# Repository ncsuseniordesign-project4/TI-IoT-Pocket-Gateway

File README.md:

# TI-IoT-Pocket-Gateway

Please see the [wiki](https://github.com/ncsuseniordesign-project4/TI-IoT-Pocket-Gateway/wiki) as well!

## Hardware

Hardware design files can be found under the `hardware` folder. You will need AutoCAD Eagle to modify these files.

CAM Data:
   The up to day CAM outputs are in the zipped file "IoT_Pocket_Gateway_Final.zip". 

## Software

Demo scripts, testing tools, etc can be found under the `software` folder, including a simple demo web app for communicating with a remote device using the Azure IoT Hub.

## Configuration

A `systemd` service for modem configuration / management can be found under the `configuration` folder. The various demo scripts in the `software` folder also provide examples showing how the buttons and LEDs can be used. Please see the [wiki](https://github.com/ncsuseniordesign-project4/TI-IoT-Pocket-Gateway/wiki) as well!

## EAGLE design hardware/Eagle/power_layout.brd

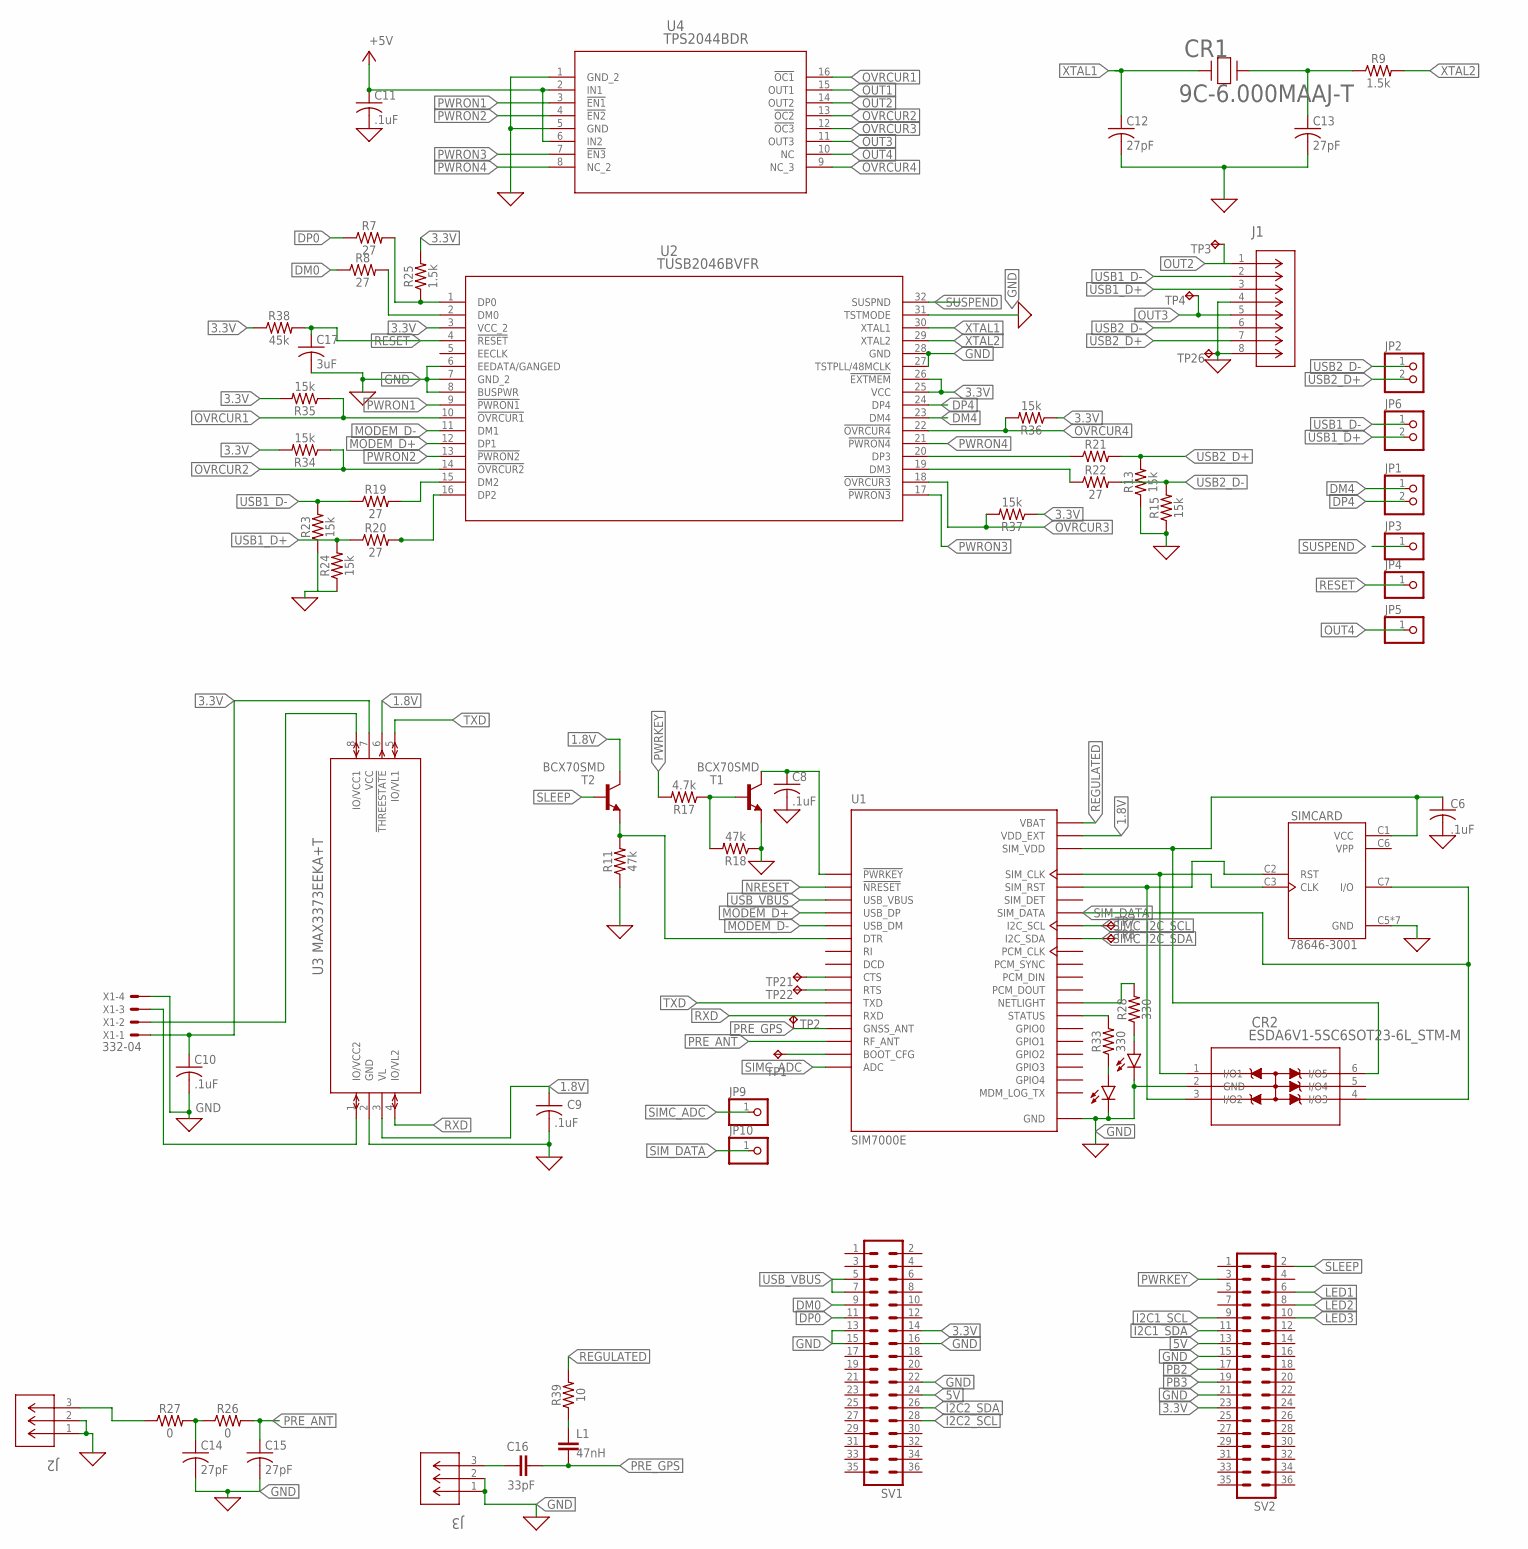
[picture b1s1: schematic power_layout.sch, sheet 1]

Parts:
C6, C8, C9, C10, C11: .1uF; C0805
C12, C13, C14, C15: 27pF; C0603
C16: 33pF; C0603K
C17: 3uF; C0805
CR1: 9C-6.000MAAJ-T; CRYSTAL_TXC_9C_TXC
CR2: ESDA6V1-5SC6SOT23-6L_STM-M; SOT23-6L_STM-M
D4, D5: Yellow; LED-0603
J1: AU-Y1008-2; CONN_AU-Y1008-2_ASM
J2, J3: U.FL-R-SMT-1(01); CONN_-SMT-1(01)
JP1, JP2, JP6: PINHD-1X2; 1X02
JP3, JP4, JP5, JP9, JP10: PINHD-1X1; 1X01
L1: 47nH; C1608
R7, R8, R19, R20, R21, R22: 27; 0805
R9: 1.5k; 0603
R11, R18: 47k; 0603
R13, R15, R23, R24, R34, R35, R36, R37: 15k; 0805
R17: 4.7k; 0603
R25: 1.5k; 0805
R26, R27: 0; 0603
R28, R33: 330; 0603
R38: 45k; 0805
R39: 10; 0805
SIMCARD: 78646-3001; MOLEX_78646-3001
SV1, SV2: MA18-2
T1, T2: BCX70SMD; SOT23
TP1, TP3, TP4, TP7, TP8, TP21, TP22, TP26: TPTP10R; TP10R
TP2: TPTP16R; TP16R
U1: SIM7000E; SIMCON_SIM7000E
U2: TUSB2046BVFR; VF32_TEX
U3: MAX3373EEKA+T; 21-0078H
U4: TPS2044BDR; D16_TEX
X1: 332-04

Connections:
0: R11.1; also elsewhere on the board
1.8V: C9.1, T2.3 (C), U1.15 (VDD_EXT), U3.3 (VL), U3.6 (!THREESTATE)
3.3V: C10.1, R25.2, R34.2, R35.2, R36.1, R37.1, R38.1, SV1.14, SV2.23, U2.3 (VCC_2), U2.25 (VCC), U2.26 (!EXTMEM), U3.7 (VCC), X1.1; also elsewhere on the board
5V: C11.1, SV1.24, SV2.13, U4.2 (IN1), U4.6 (IN2); also elsewhere on the board
DM0: R8.1, SV1.9
DM4: JP1.1, U2.23 (DM4)
DP0: R7.1, SV1.11
DP4: JP1.2, U2.24 (DP4)
GND: C6.2, C8.2, C9.2, C10.2, C11.2, C12.2, C13.2, C14.2, C15.2, C17.2, CR2.2 (GND), D4.C, D5.C, J1.4, J1.8, J2.1, J2.2, J3.1, J3.2, R13.1, R15.1, R18.1, R23.1, R24.1, SIMCARD.C5 (GND), SIMCARD.G1 (GND), SIMCARD.G2 (GND), SIMCARD.G3 (GND), SIMCARD.G4 (GND), SIMCARD.G5 (GND), SIMCARD.G6 (GND), SV1.13, SV1.15, SV1.16, SV1.22, SV2.15, SV2.21, T1.2 (E), TP26.TP, U1.2 (GND), U1.17 (GND), U1.18 (GND), U1.29 (GND), U1.39 (GND), U1.45 (GND), U1.46 (GND), U1.54 (GND), U1.58 (GND), U1.59 (GND), U1.61 (GND), U1.62 (GND), U1.63 (GND), U1.64 (GND), U1.65 (GND), U2.6 (EEDATA/GANGED), U2.7 (GND_2), U2.8 (BUSPWR), U2.27 (TSTPLL/48MCLK), U2.28 (GND), U2.31 (TSTMODE), U3.2 (GND), U4.1 (GND_2), U4.5 (GND), X1.4; also elsewhere on the board
I2C1_SCL: SV2.9; also elsewhere on the board
I2C1_SDA: SV2.11; also elsewhere on the board
I2C2_SCL: SV1.28; also elsewhere on the board
I2C2_SDA: SV1.26; also elsewhere on the board
LED1: SV2.6; also elsewhere on the board
LED2: SV2.8; also elsewhere on the board
LED3: SV2.10; also elsewhere on the board
MODEM_D+: U1.27 (USB_DP), U2.12 (DP1)
MODEM_D-: U1.28 (USB_DM), U2.11 (DM1)
unnamed: C6.1, CR2.6 (I/O5), SIMCARD.C1 (VCC), U1.30 (SIM_VDD)
unnamed: CR2.3 (I/O2), SIMCARD.C2 (RST), U1.33 (SIM_RST)
unnamed: CR2.1 (I/O1), SIMCARD.C3 (CLK), U1.32 (SIM_CLK)
unnamed: TP1.TP, U1.6 (BOOT_CFG)
unnamed: R7.2, R25.1, U2.1 (DP0)
unnamed: C14.1, R26.1, R27.2
unnamed: R8.2, U2.2 (DM0)
unnamed: U3.8 (IO/VCC1), X1.2
unnamed: C13.1, CR1.2, R9.1
unnamed: C16.1, J3.3
unnamed: R22.1, U2.19 (DM3)
unnamed: R17.1, R18.2, T1.1 (B)
unnamed: R19.2, U2.15 (DM2)
unnamed: R20.2, U2.16 (DP2)
unnamed: TP21.TP, U1.7 (CTS)
unnamed: R21.1, U2.20 (DP3)
unnamed: C8.1, T1.3 (C), U1.1 (!PWRKEY)
unnamed: L1.1, R39.1
unnamed: R28.2, U1.52 (NETLIGHT)
unnamed: D4.A, R28.1
unnamed: TP22.TP, U1.8 (RTS)
unnamed: R33.2, U1.66 (STATUS)
unnamed: J2.3, R27.1
unnamed: R11.2, T2.2 (E), U1.3 (DTR)
unnamed: D5.A, R33.1
unnamed: U3.1 (IO/VCC2), X1.3
NRESET: U1.16 (!NRESET); also elsewhere on the board
OUT1: U4.15 (OUT1)
OUT2: J1.1, TP3.TP, U4.14 (OUT2)
OUT3: J1.5, TP4.TP, U4.11 (OUT3)
OUT4: JP5.1, U4.10 (NC)
OVRCUR1: R35.1, U2.10 (!OVRCUR1), U4.16 (!OC1)
OVRCUR2: R34.1, U2.14 (!OVRCUR2), U4.13 (!OC2)
OVRCUR3: R37.2, U2.18 (!OVRCUR3), U4.12 (!OC3)
OVRCUR4: R36.2, U2.22 (!OVRCUR4), U4.9 (NC_3)
PB2: SV2.17; also elsewhere on the board
PB3: SV2.19; also elsewhere on the board
PRE_ANT: C15.1, R26.2, U1.60 (RF_ANT)
PRE_GPS: C16.2, L1.2, TP2.TP, U1.53 (GNSS_ANT)
PWRKEY: R17.2, SV2.3
PWRON1: U2.9 (!PWRON1), U4.3 (!EN1)
PWRON2: U2.13 (!PWRON2), U4.4 (!EN2)
PWRON3: U2.17 (!PWRON3), U4.7 (!EN3)
PWRON4: U2.21 (!PWRON4), U4.8 (NC_2)
REGULATED: R39.2, U1.55 (VBAT), U1.56 (VBAT), U1.57 (VBAT); also elsewhere on the board
RESET: C17.1, JP4.1, R38.2, U2.4 (!RESET)
RXD: U1.10 (RXD), U3.4 (IO/VL2)
SIMC_ADC: JP9.1, U1.25 (ADC)
SIMC_I2C_SCL: TP7.TP, U1.38 (I2C_SCL)
SIMC_I2C_SDA: TP8.TP, U1.37 (I2C_SDA)
SIM_DATA: CR2.4 (I/O3), JP10.1, SIMCARD.C7 (I/O), U1.31 (SIM_DATA)
SLEEP: SV2.2, T2.1 (B)
SUSPEND: JP3.1, U2.32 (SUSPND)
TXD: U1.9 (TXD), U3.5 (IO/VL1)
USB1_D+: J1.3, JP6.2, R20.1, R24.2
USB1_D-: J1.2, JP6.1, R19.1, R23.2
USB2_D+: J1.7, JP2.2, R13.2, R21.2
USB2_D-: J1.6, JP2.1, R15.2, R22.2
USB_VBUS: SV1.5, SV1.7, U1.24 (USB_VBUS)
VPP: SIMCARD.C6 (VPP)
XTAL1: C12.1, CR1.1, U2.30 (XTAL1)
XTAL2: R9.2, U2.29 (XTAL2)

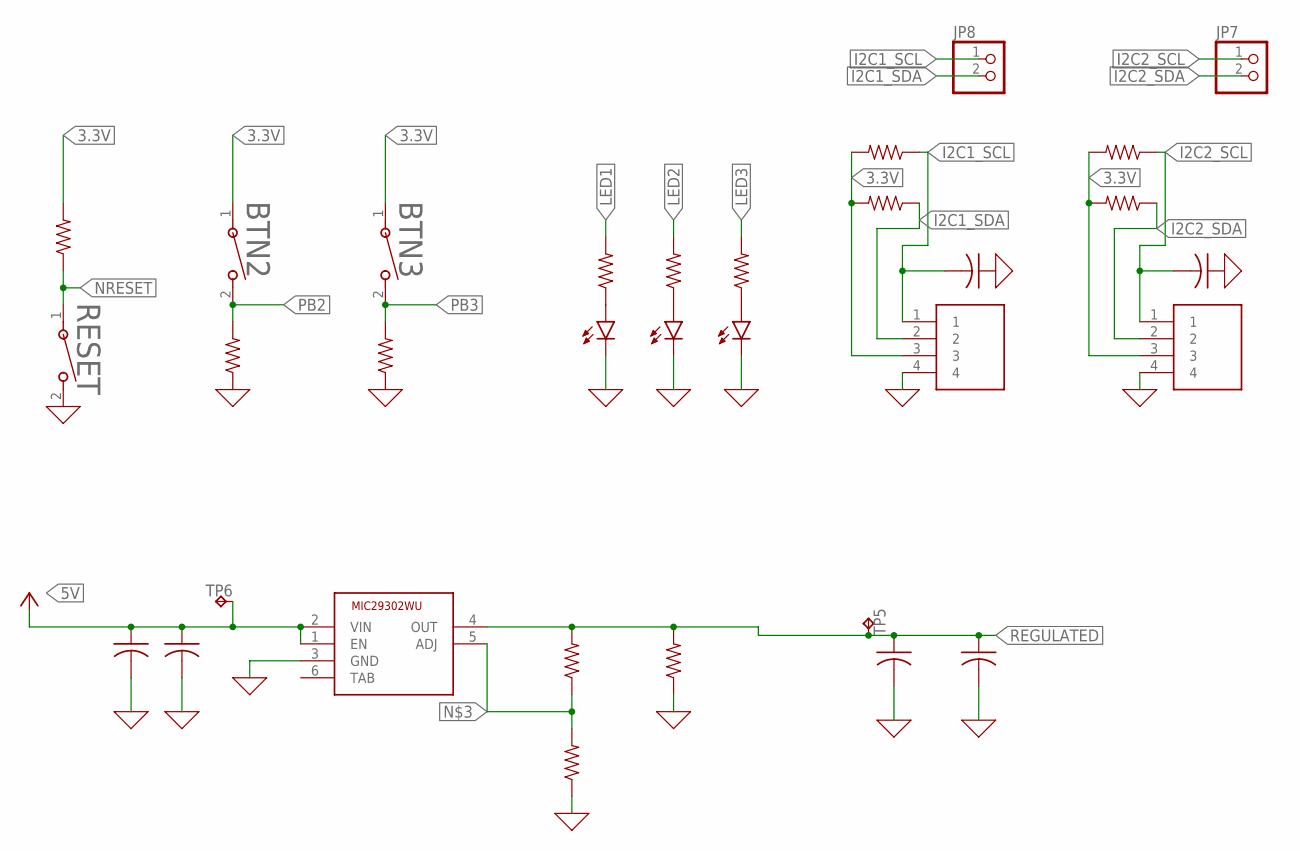
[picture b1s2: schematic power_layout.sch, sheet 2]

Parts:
BTN2, BTN3: PTS636SM25F; SW2_PTS636_SM25F_SMTR_LFS_CNK
C1: 100uF; C0805
C2, C7: 0.1uF; C0805
C3: 330uF; C1210
C4: 1uF; C0805
C5: 100nF; C0805
D1: RED; LED-1206
D2: GREEN; LED-1206
D3: BLUE; LED-1206
GROVE1, GROVE2: 640456-4; TE_640456-4
JP7, JP8: PINHD-1X2; 1X02
POWER_SUPPLY: MIC29302WU; TO263-5
R1: 60.4; 0805
R2, R3: 180; 0805
R4: 47k; 0805
R5: 100k; 0805
R6: 1500; 0805
R10, R14, R16, R29, R30, R31, R32: 4700; 0805
RESET: PTS636SM25F; SW2_PTS636_SM25F_SMTR_LFS_CNK
TP5, TP6: TPTP10R; TP10R

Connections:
0: RESET.2; also elsewhere on the board
3.3V: BTN2.1, BTN3.1, GROVE1.3, GROVE2.3, R10.2, R29.2, R30.2, R31.2, R32.2; also elsewhere on the board
5V: C1.1, C4.1, POWER_SUPPLY.1 (EN), POWER_SUPPLY.2 (VIN), TP6.TP; also elsewhere on the board
GND: C1.2, C2.1, C3.2, C4.2, C5.2, C7.1, D1.C, D2.C, D3.C, GROVE1.4, GROVE2.4, POWER_SUPPLY.3 (GND), R4.1, R6.1, R14.1, R16.1; also elsewhere on the board
I2C1_SCL: C2.2, GROVE1.1, JP8.1, R29.1; also elsewhere on the board
I2C1_SDA: GROVE1.2, JP8.2, R30.1; also elsewhere on the board
I2C2_SCL: C7.2, GROVE2.1, JP7.1, R31.1; also elsewhere on the board
I2C2_SDA: GROVE2.2, JP7.2, R32.1; also elsewhere on the board
LED1: R3.2; also elsewhere on the board
LED2: R2.2; also elsewhere on the board
LED3: R1.2; also elsewhere on the board
unnamed: POWER_SUPPLY.5 (ADJ), R4.2, R5.1
unnamed: D3.A, R1.1
unnamed: D2.A, R2.1
unnamed: D1.A, R3.1
NRESET: R10.1, RESET.1; also elsewhere on the board
PB2: BTN2.2, R14.2; also elsewhere on the board
PB3: BTN3.2, R16.2; also elsewhere on the board
REGULATED: C3.1, C5.1, POWER_SUPPLY.4 (OUT), R5.2, R6.2, TP5.TP; also elsewhere on the board

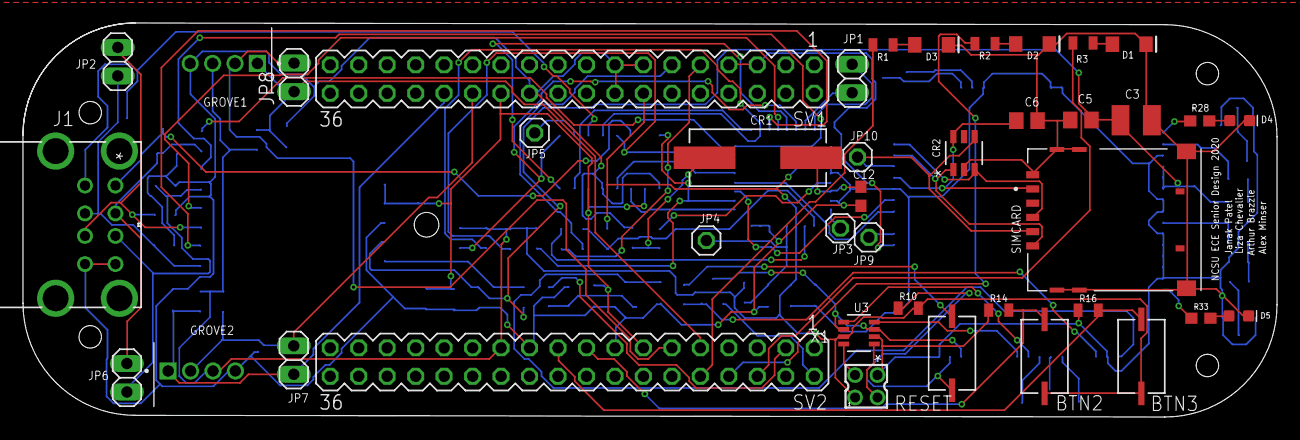
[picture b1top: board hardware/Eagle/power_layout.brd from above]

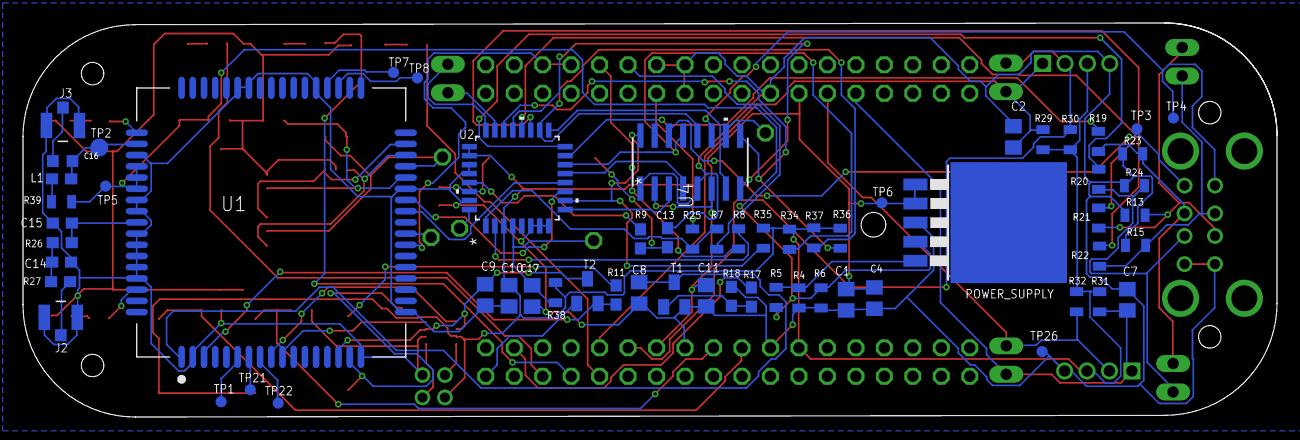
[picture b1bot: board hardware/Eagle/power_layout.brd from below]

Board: 2 copper layers, 111.9 x 35.2 mm, 103 parts (63 on the bottom side), 82 nets.

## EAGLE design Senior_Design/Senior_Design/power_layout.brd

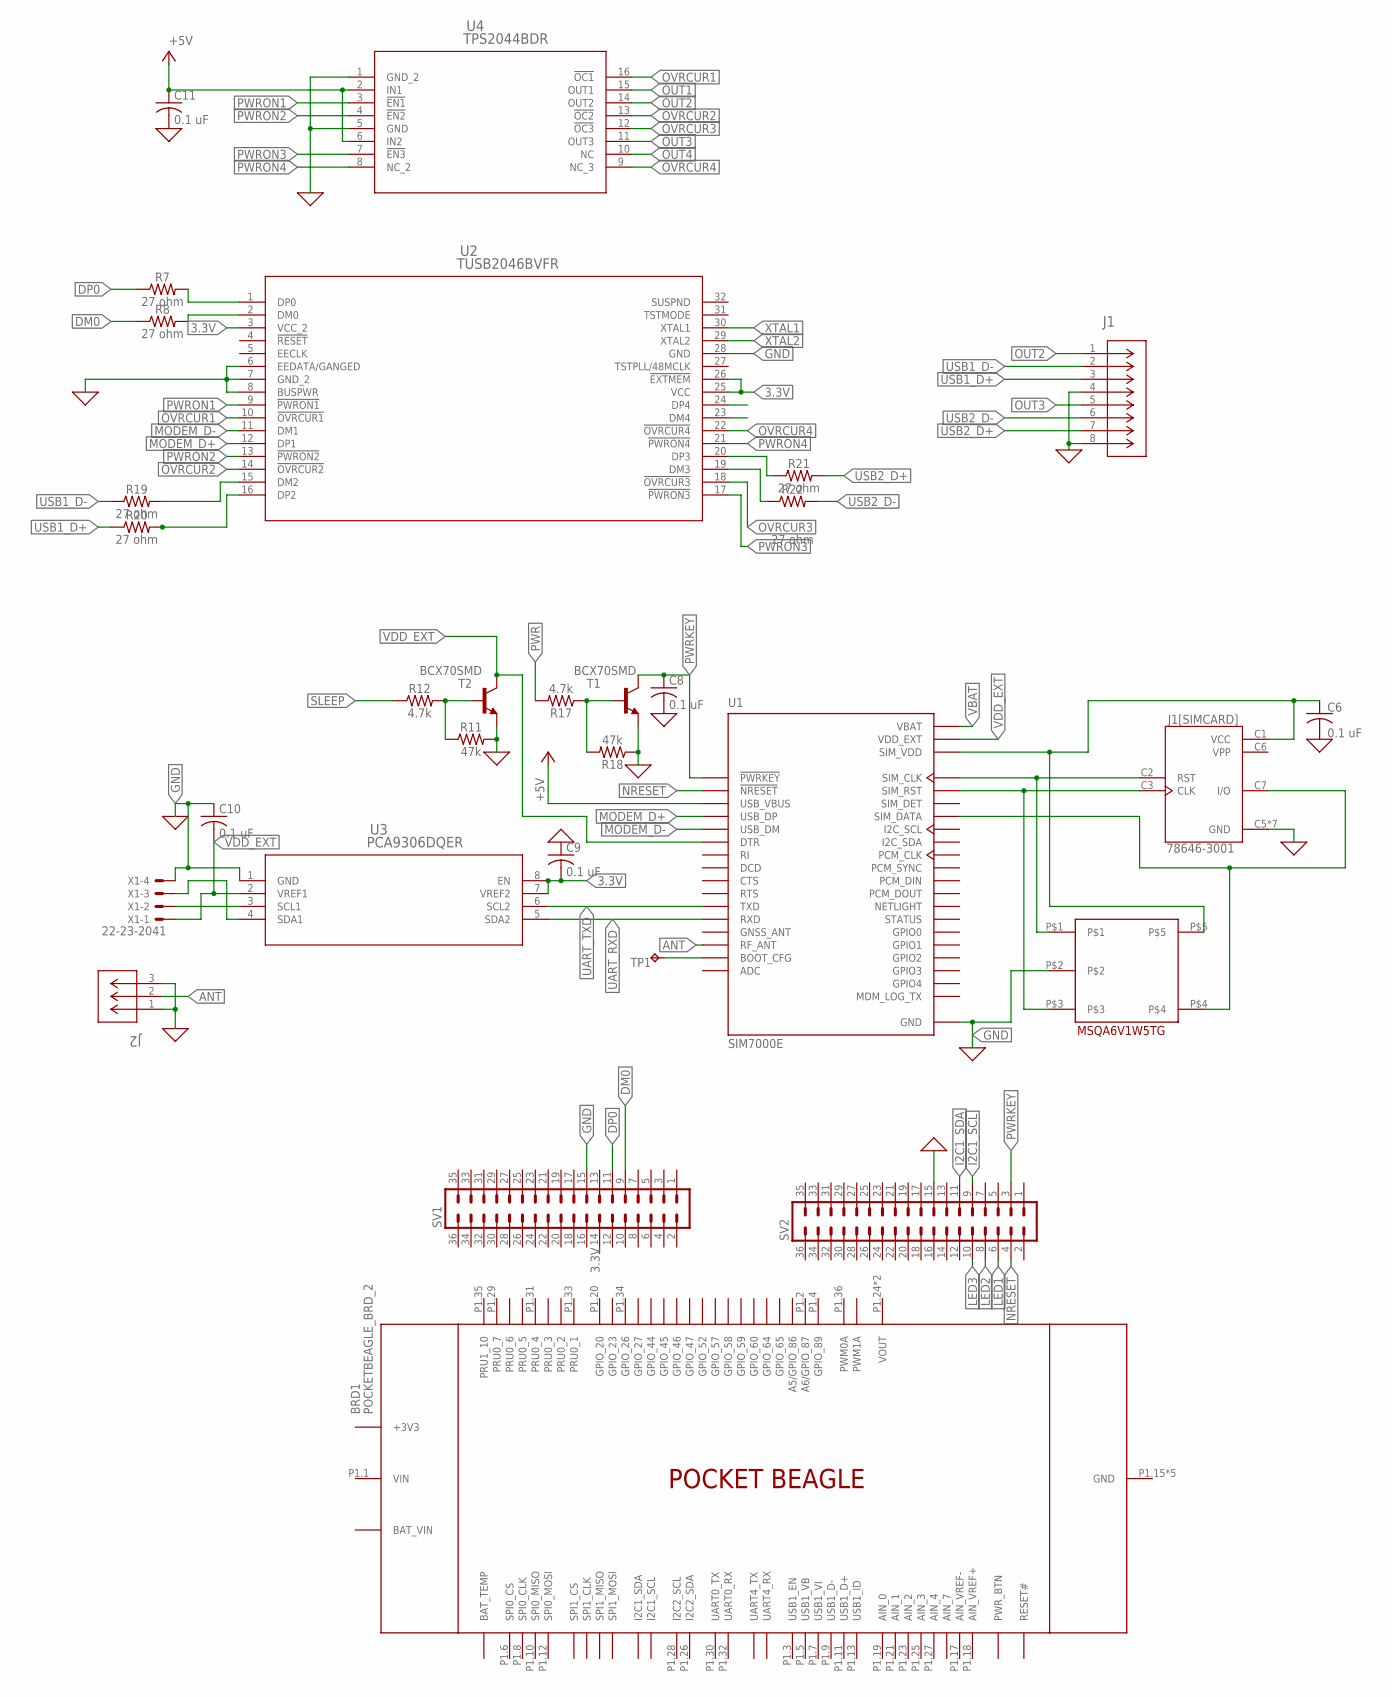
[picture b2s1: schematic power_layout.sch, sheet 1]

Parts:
BRD1: POCKETBEAGLE_BRD_2; POCKETBEAGLE_BRD
C6, C8, C9, C10, C11: 0.1 uF; C0805
J1: AU-Y1008-2; CONN_AU-Y1008-2_ASM
J1[SIMCARD]: 78646-3001; MOLEX_78646-3001
J2: U.FL-R-SMT-1(01); CONN_-SMT-1(01)
R7, R8, R19, R20, R21, R22: 27 ohm; 0805
R11, R18: 47k; 0603
R12, R17: 4.7k; 0603
SV1, SV2: MA18-2
T1, T2: BCX70SMD; SOT23
TP1: TPPAD1-13; P1-13
U1: SIM7000E; SIMCON_SIM7000E
U2: TUSB2046BVFR; VF32_TEX
U3: PCA9306DQER; DQE8
U4: TPS2044BDR; D16_TEX
U$1: MSQA6V1W5T2G; SOT-23-5_M5
X1: 22-23-2041

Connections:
0: C11.2, U2.6 (EEDATA/GANGED), U2.7 (GND_2), U2.8 (BUSPWR)
3.3V: C9.2, SV1.14, U2.3 (VCC_2), U2.25 (VCC), U2.26 (!EXTMEM), U3.7 (VREF2), U3.8 (EN)
+5V: C11.1, U1.24 (USB_VBUS), U4.2 (IN1), U4.6 (IN2); also elsewhere on the board
ANT: J2.2, U1.60 (RF_ANT)
DM0: R8.1, SV1.9
DP0: R7.1, SV1.11
GND: C6.2, C8.2, C9.1, C10.1, J1.4, J1.8, J1[SIMCARD].C5 (GND), J1[SIMCARD].G1 (GND), J1[SIMCARD].G2 (GND), J1[SIMCARD].G3 (GND), J1[SIMCARD].G4 (GND), J1[SIMCARD].G5 (GND), J1[SIMCARD].G6 (GND), J2.1, J2.3, R11.2, R18.1, SV1.15, SV2.15, T1.2 (E), T2.2 (E), U1.2 (GND), U1.17 (GND), U1.18 (GND), U1.29 (GND), U1.39 (GND), U1.45 (GND), U1.46 (GND), U1.54 (GND), U1.58 (GND), U1.59 (GND), U1.61 (GND), U1.62 (GND), U1.63 (GND), U1.64 (GND), U1.65 (GND), U2.28 (GND), U3.1 (GND), U4.1 (GND_2), U4.5 (GND), U$1.P$2, X1.4; also elsewhere on the board
I2C1_SCL: SV2.9; also elsewhere on the board
I2C1_SDA: SV2.11; also elsewhere on the board
LED1: SV2.6; also elsewhere on the board
LED2: SV2.8; also elsewhere on the board
LED3: SV2.10; also elsewhere on the board
MODEM_D+: U1.27 (USB_DP), U2.12 (DP1)
MODEM_D-: U1.28 (USB_DM), U2.11 (DM1)
unnamed: C6.1, J1[SIMCARD].C1 (VCC), U1.30 (SIM_VDD), U$1.P$5
unnamed: J1[SIMCARD].C3 (CLK), U1.33 (SIM_RST), U$1.P$3
unnamed: J1[SIMCARD].C2 (RST), U1.32 (SIM_CLK), U$1.P$1
unnamed: J1[SIMCARD].C7 (I/O), U1.31 (SIM_DATA), U$1.P$4
unnamed: TP1.TP, U1.6 (BOOT_CFG)
unnamed: R7.2, U2.1 (DP0)
unnamed: R8.2, U2.2 (DM0)
unnamed: U3.3 (SCL1), X1.2
unnamed: U3.4 (SDA1), X1.3
unnamed: R11.1, R12.2, T2.1 (B)
unnamed: R17.1, R18.2, T1.1 (B)
unnamed: R19.2, U2.15 (DM2)
unnamed: R20.2, U2.16 (DP2)
unnamed: R21.1, U2.20 (DP3)
unnamed: R22.1, U2.19 (DM3)
NRESET: SV2.4, U1.16 (!NRESET); also elsewhere on the board
OUT1: U4.15 (OUT1)
OUT2: J1.1, U4.14 (OUT2)
OUT3: J1.5, U4.11 (OUT3)
OUT4: U4.10 (NC)
OVRCUR1: U2.10 (!OVRCUR1), U4.16 (!OC1)
OVRCUR2: U2.14 (!OVRCUR2), U4.13 (!OC2)
OVRCUR3: U2.18 (!OVRCUR3), U4.12 (!OC3)
OVRCUR4: U2.22 (!OVRCUR4), U4.9 (NC_3)
PWR: R17.2
PWRKEY: C8.1, SV2.3, T1.3 (C), U1.1 (!PWRKEY)
PWRON1: U2.9 (!PWRON1), U4.3 (!EN1)
PWRON2: U2.13 (!PWRON2), U4.4 (!EN2)
PWRON3: U2.17 (!PWRON3), U4.7 (!EN3)
PWRON4: U2.21 (!PWRON4), U4.8 (NC_2)
SLEEP: R12.1
UART_RXD: U1.10 (RXD), U3.5 (SDA2)
UART_TXD: U1.9 (TXD), U3.6 (SCL2)
USB1_D+: J1.3, R20.1
USB1_D-: J1.2, R19.1
USB2_D+: J1.7, R21.2
USB2_D-: J1.6, R22.2
VBAT: U1.55 (VBAT), U1.56 (VBAT), U1.57 (VBAT); also elsewhere on the board
VDD_EXT: C10.2, T2.3 (C), U1.3 (DTR), U1.15 (VDD_EXT), U3.2 (VREF1), X1.1
VPP: J1[SIMCARD].C6 (VPP)
XTAL1: U2.30 (XTAL1)
XTAL2: U2.29 (XTAL2)

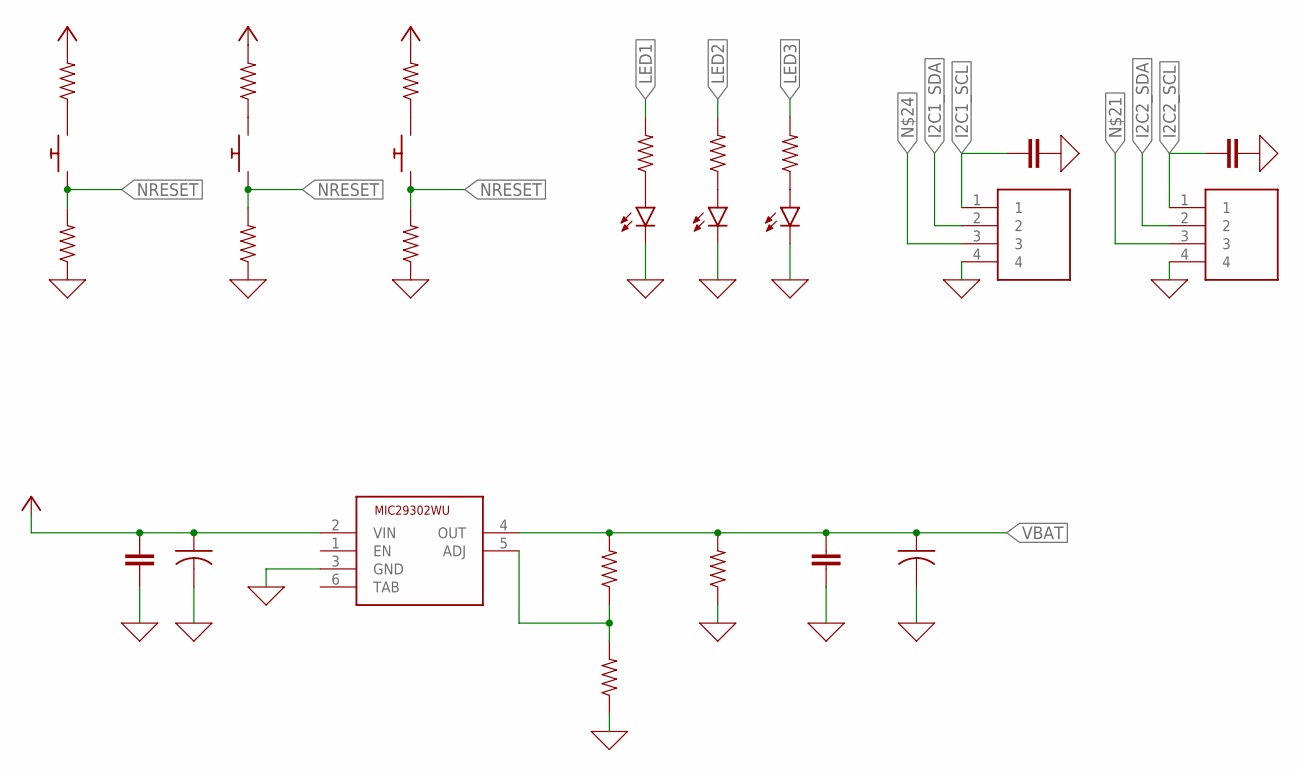
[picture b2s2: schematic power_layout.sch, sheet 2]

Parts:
C1: 100 uF; C2.5-3
C2, C7: 0.1uF; C2.5-3
C3: 330 uF; C2.5-3
C4: 1 uF; C025-024X044
C5: 100 nF; C025-024X044
D1, D2, D3: LED-3MM-NO_SILK; LED_3MM-NS
GROVE1: 640456-4; TE_640456-4
IC1: MIC29302WU; TO263-5
J4[GROVE]: 640456-4; TE_640456-4
R1: 10 ohm; 0805
R2, R3: 60 ohm; 0805
R4: 47k ohm; 0805
R5: 100k ohm; 0805
R6: 470 ohm; 0805
R9, R13, R15: 4.7k ohm; 0805
R10, R14, R16: 0805
SW1, SW2, SW3: SWITCH_PUSHBUTTONSOFTTOUCHSMD_SJ; PUSHBUTTON_SMD_SJ

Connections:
+5V: C1.1, C4.1, IC1.2 (VIN), R9.2, R13.2, R15.2; also elsewhere on the board
GND: C1.2, C2.1, C3.2, C4.2, C5.2, C7.1, D1.K (C), D2.K (C), D3.K (C), GROVE1.4, IC1.3 (GND), J4[GROVE].4, R4.1, R6.1, R10.1, R14.1, R16.1; also elsewhere on the board
I2C1_SCL: C2.2, GROVE1.1; also elsewhere on the board
I2C1_SDA: GROVE1.2; also elsewhere on the board
I2C2_SCL: C7.2, J4[GROVE].1
I2C2_SDA: J4[GROVE].2
LED1: R3.2; also elsewhere on the board
LED2: R2.2; also elsewhere on the board
LED3: R1.2; also elsewhere on the board
unnamed: IC1.5 (ADJ), R4.2, R5.1
unnamed: D3.A, R1.1
unnamed: D2.A, R2.1
unnamed: D1.A, R3.1
unnamed: R9.1, SW1.P$2
unnamed: R13.1, SW2.P$2
unnamed: R15.1, SW3.P$2
NRESET: R10.2, R14.2, R16.2, SW1.P$1, SW2.P$1, SW3.P$1; also elsewhere on the board
VBAT: C3.1, C5.1, IC1.4 (OUT), R5.2, R6.2; also elsewhere on the board

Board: 2 copper layers, 57 parts (4 on the bottom side), 57 nets, no tracks yet.

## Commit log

2020-04-02 Added eagle stuff
2020-04-02 Design Day Demo Scripts
2020-04-04 Update README.md
    PCB Design
    Change Notes:
    -4/4/2020 11AM: Added pocketbeagle pinout to document with library. I will modify it but the part can hang out as a reference.
    Work to do:
    -Voltage Regulator: I think we need a SOT-23 form factor chip for size reasons. The current one may still fit though.
    -SMD pin fooprint: I need to convert the pocketBeagle(PB) pins to an SMD .1" pin header for the bottom side connection to the PB.
2020-04-04 Arthur's 1st Push
    Annotated on Readme as 4/4/2020 11AM push
2020-04-09 Schematic & Layout Updates
    Updates made prior to poster publishing for Demo Day Poster!
2020-04-10 Create LICENSE
2020-04-12 Create folders for test code and demo
    This commit reorganizes the demo code into two folders. The first,
    'SoftwareTest', for test implementations, and the second,
    '484-TechDemo', for the software written and used in the ECE-484 end of
    semester Design Day Demo.
2020-04-12 Add config and LED support
    This commit adds configuration support to the program so that the source
    code does not need to be edited to change the IoT Device primary key or
    the time delay between program loop iterations. This makes it easier to
    use the program in multiple environments and removes the risk of
    accidentally committing secret keys to the repository.
    RGB LED support has also been added to the program. Now any data read
2020-04-12 Add SIM7000A service files
    This commit adds a systemd service file and associated scripts for
    connecting and disconnecting from the cellular modem. With this service
    properly installed the PocketBeagle can automatically start the network
    on startup or simply provide a more convenient way to manually start and
    stop the network. A configuration file for the Things Mobile network has
    also been provided.
2020-04-30 added network scan python script
2020-08-27 Add files via upload
    Upload at beginning of pre-CDR work. Minimal changes since April (addition of UART level shifter for sim7000)
2020-08-30 Added a bit more detail to the modem design
2020-09-01 Add files via upload
    End of Night Upload as we work towards CDR layout.
    My to-do list (from memory)
    -Add crystal oscillator to USB hub w/capacitors
    -repalce LEDS with smd leds
    -change all passives to 603 or 605 sizes
    -walk through voltage levels with Alex before layout
2020-09-02 Add files via upload
    Schematic Reflects all changes as discussed in Sep 1st HW meeting. Layout will begin tomorrow.
2020-09-03 Add files via upload
    Another push inbound
2020-09-03 Add files via upload
    Nightly progress pre-CDR
    -Still finishing Layout
    ~2 hours of layout left until first draft complete
2020-09-03 Added values to passives
2020-09-03 Add 485 Lab Bench Demo
    Adds ECE 485 Lab Bench Demo code. The Lab Bench Demo allows a user to
    control the green and blue channels of the RGB LED on the TechLab cape
    remotely via Azure. It also provides a way for the user to remotely
    query IP information.
2020-09-03 Add files via upload
    Final Design files prior to CDR!
    Includes schematic and layout
    -Needs final review prior to ordering
2020-09-08 Added Pre-PCB Review Changes
    Polishing of post-CDR design
2020-09-09 PCB Review 2 meeting Push
2020-09-10 Hopefully Final Changes Pre-Alpha Purchase
    *Still need to generate GERBERS*
2020-09-11 Added team names to pcb and created gerber files
2020-09-11 Fixed issues w/ gerber files
2020-09-14 Alpha Order Design Changes
    Incorporated all PCB Review design changes
2020-09-14 Updated C3 Size and regenerated CAM
    Part swap pre-ordering
2020-09-14 Updating missing part values
    Alex had assigned these before but I wrote over them on accident :)
2020-10-19 Beta Boar Spin Files
    Implemented board revisions from Alpha board.
2020-10-19 Beta Board Spin Upload
    Implemented Alpha Board Changes.
    Cleaned up folder to remove old CAM outputs
2020-10-21 Add files via upload
    This push includes the changes from Dr Pitts' Review and is THE Beta Board for purchasing.
    -Cam files are processed in the folder "Beta Spin"
2020-11-16 added button script and the main gateway script used in the final demo.
2020-11-16 modified the package.json for the pocketbeagle node.js script. Added the XBee ph sensor scripts
2020-11-17 Adding Final Design Files
    Incorporated all changes from Beta Assembly
2020-11-17 added Ethernet and WiFi final demo scripts. Removed sensitive data from the broker script.
2020-11-17 Demo website for showcasing TI IoT Pocket Gateway
    Implements a simple Blazor server side app for demoing and testing the
    TI IoT Pocket Gateway functionality using Azure. Functionality is
    implemented in the 'IotHub.razor' and 'IotHub.razor.cs'.
2020-11-17 Adding PDF's of schematic and layout
2020-11-17 Uploading Enclosure Design Files and .stl for 3D printing
2020-11-18 Reorganize repo for project conclusion
    Concludes the NCSU senior design work for the TI IoT Pocket Gateway.
    Repository has been reorganized for better navigation and cleaned up to
    remove old files.
2020-11-18 Add Final Document submission

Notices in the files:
parts and their libraries:
SparkFun-LED: Licensing: Creative Commons ShareAlike 4.0 International - https://creativecommons.org/licenses/by-sa/4.0
COPYRIGHT: Copyright (C) 2018 Accelerated Designs. All rights reserved
